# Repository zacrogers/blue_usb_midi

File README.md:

# STM32 Blue Pill USB Midi Controller

USB class compliant midi implementation with stm32 blue pill

Grid keypad midi controller. 
8 step sequencer.
LCD display menu for setting parameters.

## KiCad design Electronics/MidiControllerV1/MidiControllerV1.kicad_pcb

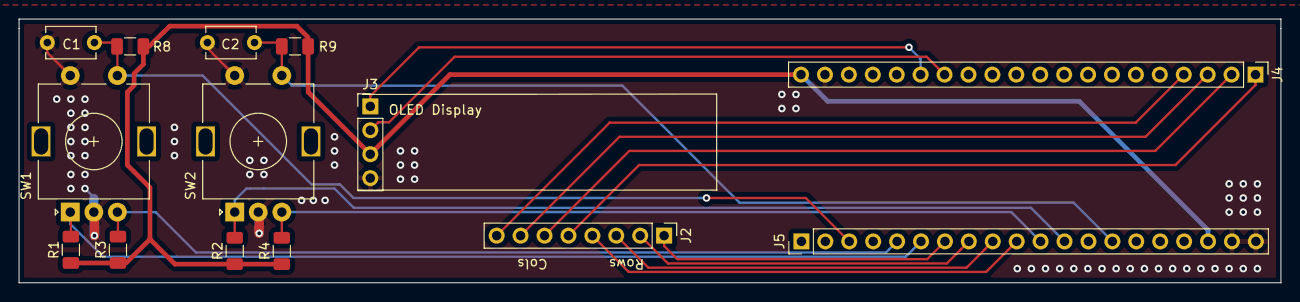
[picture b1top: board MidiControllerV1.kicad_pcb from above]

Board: 2 copper layers, 134.0 x 28.0 mm, 14 parts (0 on the bottom side), 18 nets.

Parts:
C1, C2: C; C_Disc_D5.1mm_W3.2mm_P5.00mm
J2: KeypadConnector; PinHeader_1x08_P2.54mm_Vertical
J3: OledConnector; PinHeader_1x04_P2.54mm_Vertical
J4: BluePillHeaderA; PinHeader_1x20_P2.54mm_Vertical
J5: BluepillHeaderB; PinHeader_1x20_P2.54mm_Vertical
R1, R2, R3, R4, R8, R9: R; R_1206_3216Metric
SW1, SW2: Rotary_Encoder_Switch; RotaryEncoder_Alps_EC11E-Switch_Vertical_H20mm

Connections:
+3V3: J3.3, J4.20, J5.18, R1.1, R2.1, R3.1, R4.1, R8.1, R9.1
ENC1A: J5.6, R1.2, SW1.A
ENC1B: J5.5, R3.2, SW1.B
ENC1_SW: C1.1, J5.3, R8.2, SW1.S1
ENC2A: J5.12, R2.2, SW2.A
ENC2B: J5.11, R4.2, SW2.B
ENC2_SW: C2.1, J5.14, R9.2, SW2.S1
GND: C1.2, C2.2, J3.4, J4.19, J5.19, J5.20, SW1.C, SW1.S2, SW2.C, SW2.S2
KP_C1: J2.5, J4.1
KP_C2: J2.6, J4.2
KP_C3: J2.7, J4.3
KP_C4: J2.8, J4.4
KP_R1: J2.1, J5.7
KP_R2: J2.2, J5.8
KP_R3: J2.3, J5.9
KP_R4: J2.4, J5.10
LCD_SCL: J3.2, J4.14
LCD_SDA: J3.1, J4.15

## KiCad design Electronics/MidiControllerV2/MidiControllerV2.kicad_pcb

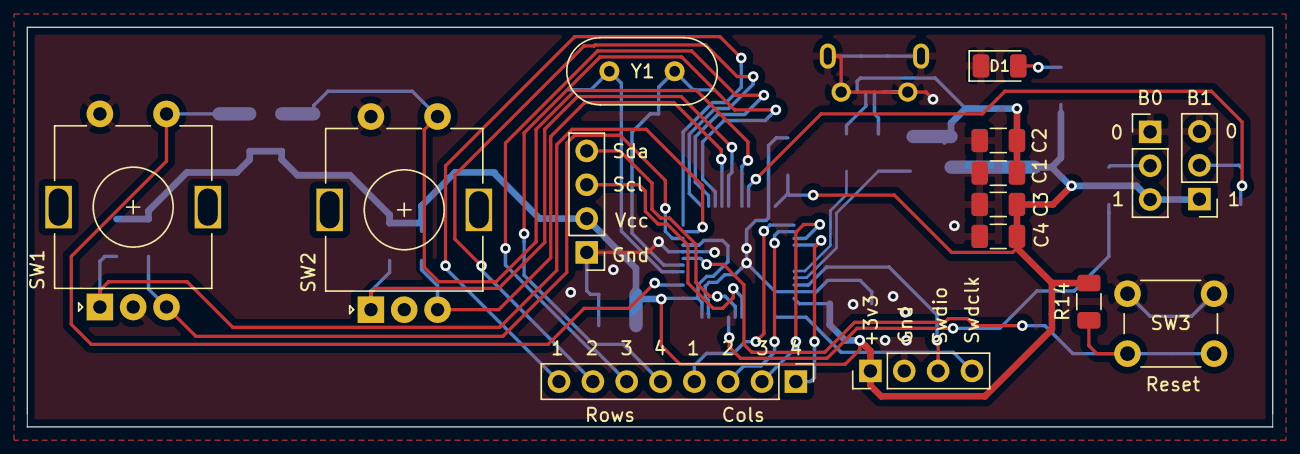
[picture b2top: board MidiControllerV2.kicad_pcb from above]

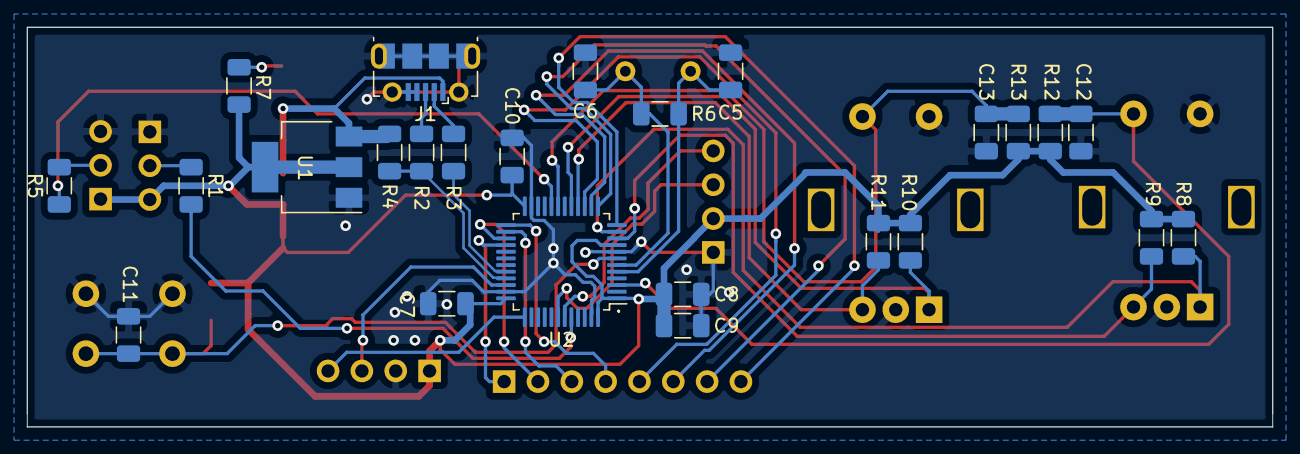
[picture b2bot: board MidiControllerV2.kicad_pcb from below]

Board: 2 copper layers, 93.5 x 30.0 mm, 40 parts (25 on the bottom side), 33 nets.

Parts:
C1, C2, C3, C4, C5, C6, C7, C8, C9, C10, C11, C12, C13: C; C_1206_3216Metric
D1: LED; LED_1206_3216Metric
J1: USB_B_Micro; USB_Micro-B_Molex-105017-0001
J2: BOOT0_H; PinHeader_1x03_P2.54mm_Vertical
J3: BOOT1_H; PinHeader_1x03_P2.54mm_Vertical
J4, J6: Conn_01x04_Male; PinHeader_1x04_P2.54mm_Vertical
J5: Conn_01x08_Male; PinHeader_1x08_P2.54mm_Vertical
R1, R2, R3, R4, R5, R7, R8, R9, R10, R11, R12, R13, R14: R; R_1206_3216Metric
R6: R; C_1206_3216Metric
SW1, SW2: Encoder; RotaryEncoder_Alps_EC11E-Switch_Vertical_H20mm
SW3: SW_DPST; SW_PUSH_6mm
U1: AMS1117-3.3; SOT-223-3_TabPin2
U2: STM32F100C8Tx; LQFP-48_7x7mm_P0.5mm
Y1: Crystal; Crystal_HC18-U_Vertical

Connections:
+3V3: C3.1, C4.1, C7.1, C8.1, C9.1, C10.1, J2.3, J3.1, J4.1, J6.2, R7.1, R8.2, R9.2, R10.2, R11.2, R12.2, R13.2, R14.1, U1.2, U2.1, U2.9, U2.24, U2.36, U2.48
+5V: C1.1, C2.1, J1.1, R4.1, U1.3
BOOT0: R1.2, U2.44
BOOT1: R5.1, U2.20
ENC1A: R8.1, SW1.A, U2.11
ENC1B: R9.1, SW1.B, U2.10
ENC1_SW: C12.1, R12.1, SW1.S1, U2.3
ENC2A: R10.1, SW2.A, U2.17
ENC2B: R11.1, SW2.B, U2.16
ENC2_SW: C13.1, R13.1, SW2.S1, U2.19
GND: C1.2, C2.2, C3.2, C4.2, C5.2, C6.2, C7.2, C8.2, C9.2, C10.2, C11.2, C12.2, C13.2, D1.1, J1.4, J1.5, J1.6, J2.1, J3.3, J4.2, J6.1, SW1.C, SW1.S2, SW2.C, SW2.S2, SW3.1, U1.1, U2.8, U2.23, U2.35, U2.47
KP_C1: J5.4, U2.25
KP_C2: J5.3, U2.26
KP_C3: J5.2, U2.27
KP_C4: J5.1, U2.28
KP_R1: J5.8, U2.12
KP_R2: J5.7, U2.13
KP_R3: J5.6, U2.14
KP_R4: J5.5, U2.15
unnamed: D1.2, R7.2
unnamed: J1.2, R3.2
unnamed: J1.3, R2.2
unnamed: J2.2, R1.1
unnamed: J3.2, R5.2
OLED_SCL: J6.3, U2.42
OLED_SDA: J6.4, U2.43
OSCIN: C5.1, R6.2, U2.5, Y1.1
OSCOUT: C6.1, R6.1, U2.6, Y1.2
RESET: C11.1, R14.2, SW3.2, U2.7
SWDCLK: J4.4, U2.37
SWDIO: J4.3, U2.34
USBD+: R2.1, R4.2, U2.33
USBD-: R3.1, U2.32

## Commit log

2020-10-28 On branch master Initial commit
2020-10-28 Added gitignore file
2020-10-28 Cleaned up usbd_midi_if.h
2020-10-28 Fixed gitignore
2020-10-29 Added keypad and lcd
2020-10-29 Tidied up keypad
2020-10-29 Added rotary encoder
2020-10-29 Moved states into functions
2020-10-30 Added isr for button
2020-10-30 Keyup/keydown working
2020-10-30 Added octave offsets
2020-10-31 Added shift register
2020-11-01 #1 Menu updating working
2020-11-01 Keypad menu navigation working
2020-11-01 #2 Placed basic components
    Copied components from generic schematic of blue pill and added other parts
2020-11-02 Tidied up global variables
2020-11-02 #2 Schematic wired up
2020-11-02 Fixed screen switching
2020-11-03 Added ssd1306 library
2020-11-03 Changed display to oled
2020-11-03 #8 Tidied up oled code
2020-11-03 #10 Added sequencer main screen
2020-11-04 #3 Sequencer timer setup
2020-11-04 #11 Fixed sequencer timer blocking encoder
2020-11-04 Added play and stop symbols to sequencer screen
2020-11-04 Added mode changing and cleaned up comments
2020-11-11 Added second encoder functions
2020-11-12 #20 Changed sequencer timer to TIM4
2020-11-12 Added 3d models
2020-11-13 Updated enclosure faceplate & main body
2020-11-13 Fixed state changing
2020-11-13 #20 Second encoder added
2020-11-13 Setup sequencer encoder mapping
2020-11-13 Updated schematic
    Schematic updated to use blue pill board plugged into headers
2020-11-14 Components placed on pcb
2020-11-14 #25 Sequencer note selection kind of working
2020-11-16 #24 Laid out pcb
2020-11-18 Finished PCB layout
2020-11-19 Generated gerber files
2020-11-28 #25 Fixed encoder and button mapping
2020-11-28 Cleaned up redundant code
2020-11-30 #21 Fixed oncoder overshooting max value
2020-12-03 #27 #21 Fixed value sticking and overshooting
2020-12-03 Removed unused variables
2020-12-04 Tidied comments
2020-12-04 Refactored encoder handling
2020-12-04 #28 Tempo changing implemented
2020-12-09 #29 Fixed sequencer value sticking
2020-12-09 #28 BPM updating implemented
2020-12-09 Tidied redundant comments
2020-12-10 #23 Sequencer note off working
2020-12-10 Removed note length from sequencer
2020-12-10 Removed redundant comments
2020-12-11 #23 Sequencer note duration working
2020-12-11 Added circuit breakout schematic
2021-01-08 #32 Laid out rev1 schematic
2021-01-11 #32 Pcb v2 components placed
2021-01-11 #32 Pcb v2 power traces laid
2021-01-25 #32 Pcb layout revised
2021-04-01 #32 Updated pcb v1
